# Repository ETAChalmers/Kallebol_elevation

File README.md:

# OLD deprecated Kallebol_elevation
This project has been abandoned and is not in use

Microcontroller and code for controlling elevation of kallebolen.

The microcontroller communicates via USB.

## Communication interface
 
### commandlist

 - ELEVATION HOME START    - Start homing of the elevationcontroller, this resets the current position
 - ELEVATION HOME STOP     - Stop homing
 - ELEVATION SET *Integer* - Set current position
 - ELEVATION GOTO *Integer* - Set current target position
 - ELEVATION STOP          - kind of a E-stop to the elevation controller, the onboard motor driver should not output any voltage
 - ELEVATION STOP RESET    - turn off the stop state
 - ELEVATION GET POSITION  - returns the current position of the controller
 - ELEVATION GET TARGET    - returns the target position of the controller
 - ELEVATION GET FLAGS     - returns the states of the controller
 - ELEVATION GET ALL       - returns all of the states and positions
 - LOAD LOAD1 [ON/OFF]     - turn on/off load 1
 - LOAD LOAD2 [ON/OFF]     - turn on/off load 2
 - LED ONBOARD [ON/OFF]    - turn on/off the MCUs onboard LED
 - LED PCB0 [ON/OFF]       - turn on/off LED 0 on the PCB
 - LED PCB1 [ON/OFF]       - turn on/off LED 0 on the PCB
 - LED PCB2 [ON/OFF]       - turn on/off LED 0 on the PCB
 - LED PCB3 [ON/OFF]       - turn on/off LED 0 on the PCB
 - RFSWITCH    (TBD)

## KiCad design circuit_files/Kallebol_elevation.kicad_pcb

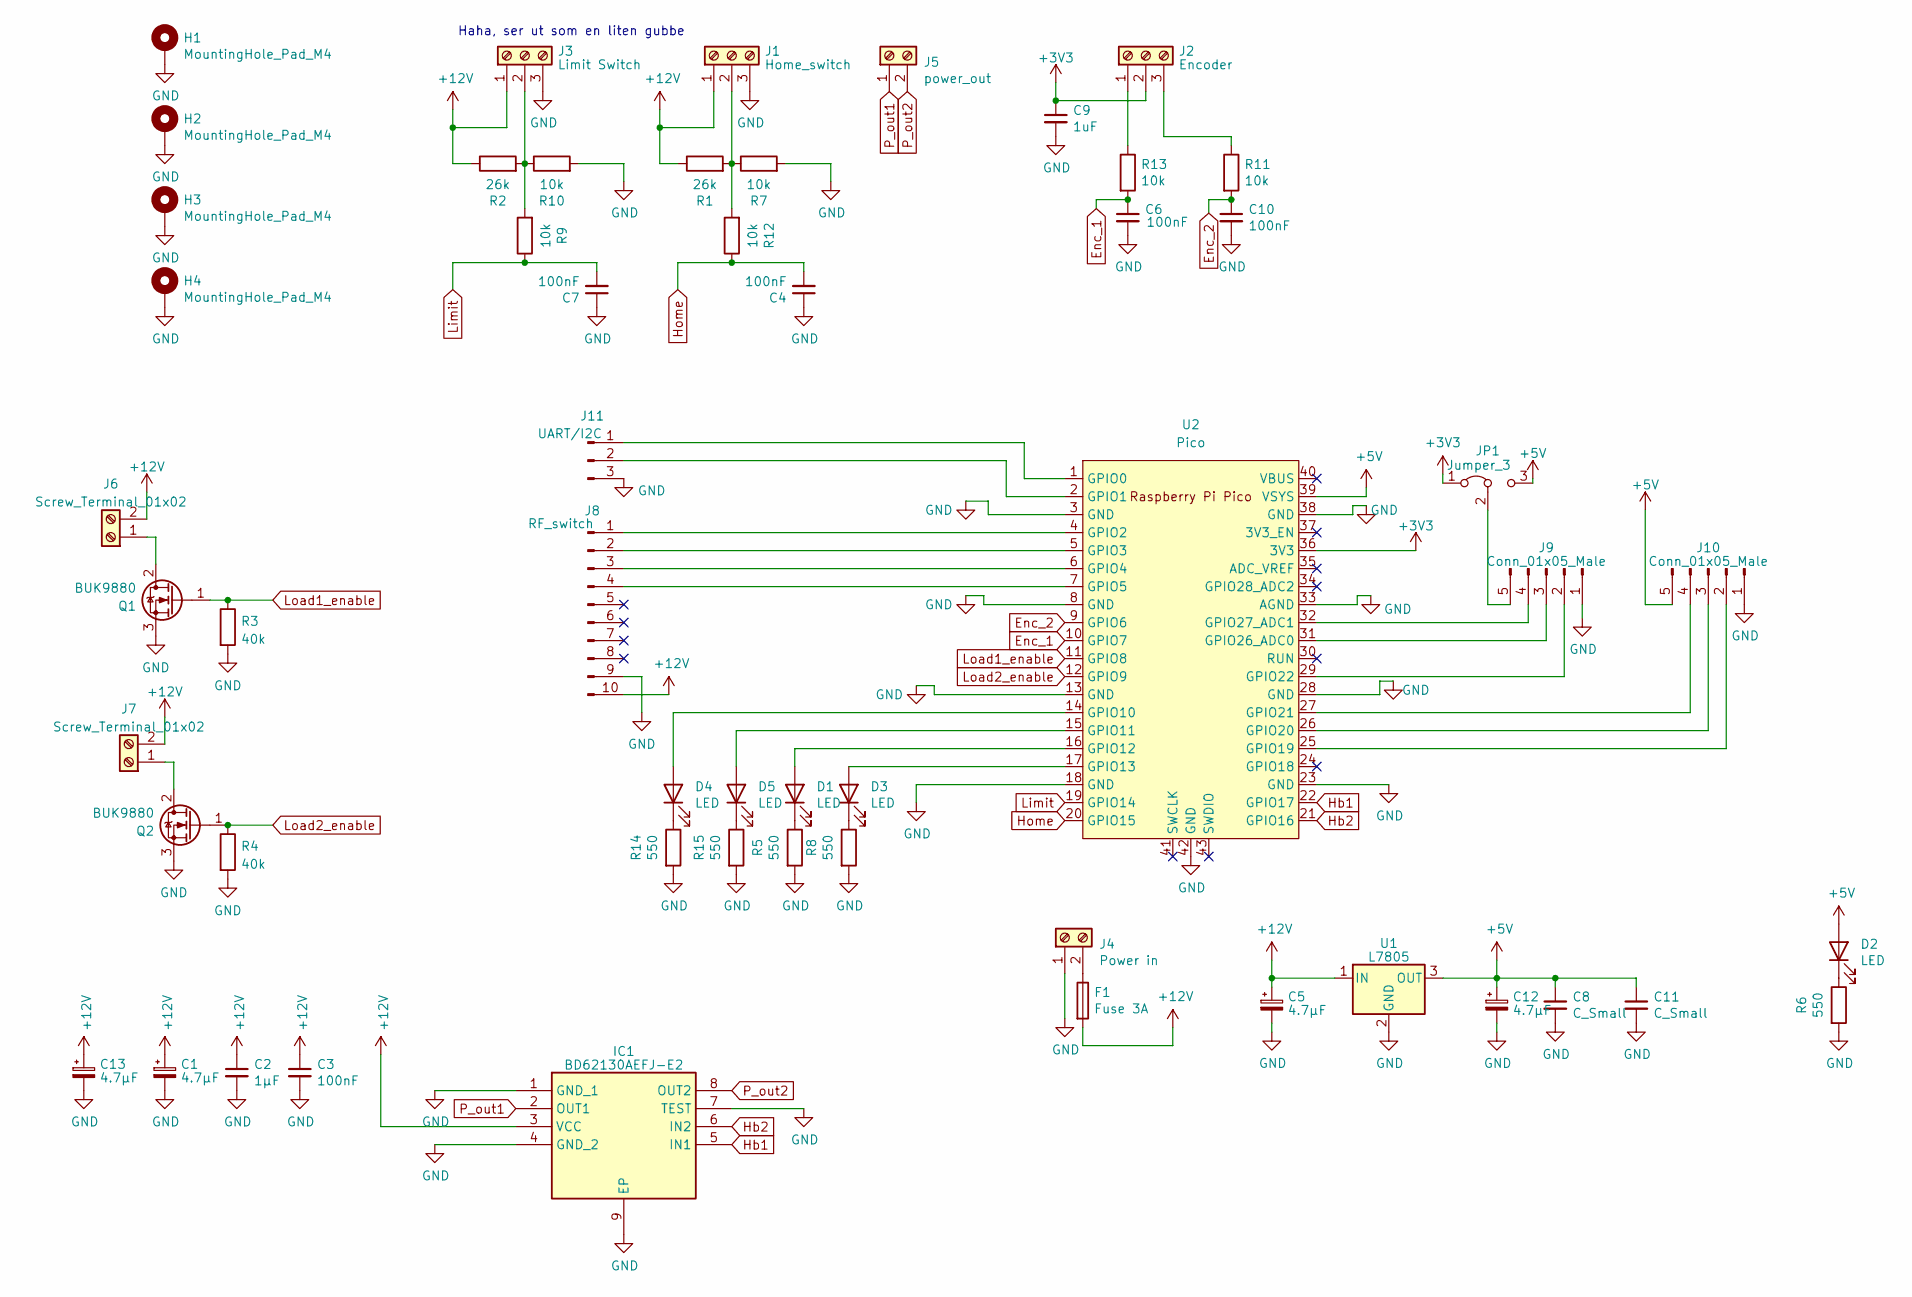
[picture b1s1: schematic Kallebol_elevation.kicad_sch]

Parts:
C1, C5, C12, C13: 4.7µF; CP_Elec_10x10
C2: 1µF; C_0603_1608Metric_Pad1.08x0.95mm_HandSolder
C3, C4, C6, C7, C10: 100nF; C_0603_1608Metric_Pad1.08x0.95mm_HandSolder
C8, C11: C_Small; C_0603_1608Metric_Pad1.08x0.95mm_HandSolder
C9: 1uF; C_0603_1608Metric_Pad1.08x0.95mm_HandSolder
D1, D2, D3, D4, D5: LED; LED_0603_1608Metric
F1: Fuse 3A; Fuseholder_Cylinder-5x20mm_Wuerth_696103101002-SMD_Horizont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
H1, H2, H3, H4: MountingHole_Pad_M4; MountingHole_4.3mm_M4_Pad
IC1: BD62130AEFJ-E2; SOIC127P600X100-9N; Mouser Part Number 755-BD62130AEFJ-E2
J1: Home_switch; TerminalBlock_Phoenix_MKDS-1,5-3_1x03_P5.00mm_Horizontal
J2: Encoder; TerminalBlock_Phoenix_MKDS-1,5-3_1x03_P5.00mm_Horizontal
J3: Limit Switch; TerminalBlock_Phoenix_MKDS-1,5-3_1x03_P5.00mm_Horizontal
J4: Power in; TerminalBlock_bornier-2_P5.08mm
J5: power_out; TerminalBlock_bornier-2_P5.08mm
J6, J7: Screw_Terminal_01x02; TerminalBlock_bornier-2_P5.08mm
J8: RF_switch; PinSocket_1x10_P2.54mm_Vertical
J9, J10: Conn_01x05_Male; PinSocket_1x05_P2.54mm_Vertical
J11: UART/I2C; PinSocket_1x03_P2.54mm_Vertical
JP1: Jumper_3; PinSocket_1x03_P2.54mm_Vertical
Q1, Q2: BUK9880; SOT-223-3_TabPin2
R1, R2: 26k; R_0603_1608Metric_Pad0.98x0.95mm_HandSolder
R3, R4: 40k; R_0603_1608Metric_Pad0.98x0.95mm_HandSolder
R5, R6, R8, R14, R15: 550; R_0603_1608Metric_Pad0.98x0.95mm_HandSolder
R7, R9, R10, R11, R12, R13: 10k; R_0603_1608Metric_Pad0.98x0.95mm_HandSolder
U1: L7805; SOT-223-3_TabPin2
U2: Pico; RPi_Pico_SMD_TH

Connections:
+3V3: C9.1, J2.2, JP1.1 (A), U2.36 (3V3)
+5V: C8.1, C11.1, C12.1, D2.2 (A), J10.5, JP1.3 (B), U1.3 (OUT), U2.39 (VSYS)
+12V: C1.1, C2.1, C3.1, C5.1, C13.1, F1.2, IC1.3 (VCC), J1.1, J3.1, J6.2, J7.2, J8.10, R1.1, R2.1, U1.1 (IN)
Enc_1: C6.1, R13.2, U2.10 (GPIO7)
Enc_2: C10.1, R11.2, U2.9 (GPIO6)
GND: C1.2, C2.2, C3.2, C4.1, C5.2, C6.2, C7.1, C8.2, C9.2, C10.2, C11.2, C12.2, C13.2, H1.1, H2.1, H3.1, H4.1, IC1.1 (GND_1), IC1.4 (GND_2), IC1.7 (TEST), IC1.9 (EP), J1.3, J3.3, J4.1, J8.9, J9.1, J10.1, J11.3, Q1.3 (S), Q2.3 (S), R3.2, R4.2, R5.2, R6.2, R7.2, R8.2, R10.2, R14.2, R15.2, U1.2 (GND), U2.3 (GND), U2.8 (GND), U2.13 (GND), U2.18 (GND), U2.23 (GND), U2.28 (GND), U2.33 (AGND), U2.38 (GND), U2.42 (GND)
Hb1: IC1.5 (IN1), U2.22 (GPIO17)
Hb2: IC1.6 (IN2), U2.21 (GPIO16)
Home: C4.2, R12.1, U2.20 (GPIO15)
Limit: C7.2, R9.1, U2.19 (GPIO14)
Load1_enable: Q1.1 (G), R3.1, U2.11 (GPIO8)
Load2_enable: Q2.1 (G), R4.1, U2.12 (GPIO9)
unnamed: D1.2 (A), U2.16 (GPIO12)
unnamed: D1.1 (K), R5.1
unnamed: D2.1 (K), R6.1
unnamed: D3.2 (A), U2.17 (GPIO13)
unnamed: D3.1 (K), R8.1
unnamed: D4.2 (A), U2.14 (GPIO10)
unnamed: D4.1 (K), R14.1
unnamed: D5.2 (A), U2.15 (GPIO11)
unnamed: D5.1 (K), R15.1
unnamed: J1.2, R1.2, R7.1, R12.2
unnamed: J2.1, R13.1
unnamed: J2.3, R11.1
unnamed: J3.2, R2.2, R9.2, R10.1
unnamed: F1.1, J4.2
unnamed: J6.1, Q1.2 (D)
unnamed: J7.1, Q2.2 (D)
unnamed: J8.1, U2.4 (GPIO2)
unnamed: J8.2, U2.5 (GPIO3)
unnamed: J8.3, U2.6 (GPIO4)
unnamed: J8.4, U2.7 (GPIO5)
unnamed: J9.2, U2.29 (GPIO22)
unnamed: J9.3, U2.31 (GPIO26_ADC0)
unnamed: J9.4, U2.32 (GPIO27_ADC1)
unnamed: J9.5, JP1.2 (C)
unnamed: J10.2, U2.25 (GPIO19)
unnamed: J10.3, U2.26 (GPIO20)
unnamed: J10.4, U2.27 (GPIO21)
unnamed: J11.1, U2.1 (GPIO0)
unnamed: J11.2, U2.2 (GPIO1)
P_out1: IC1.2 (OUT1), J5.1
P_out2: IC1.8 (OUT2), J5.2

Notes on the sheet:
Haha, ser ut som en liten gubbe

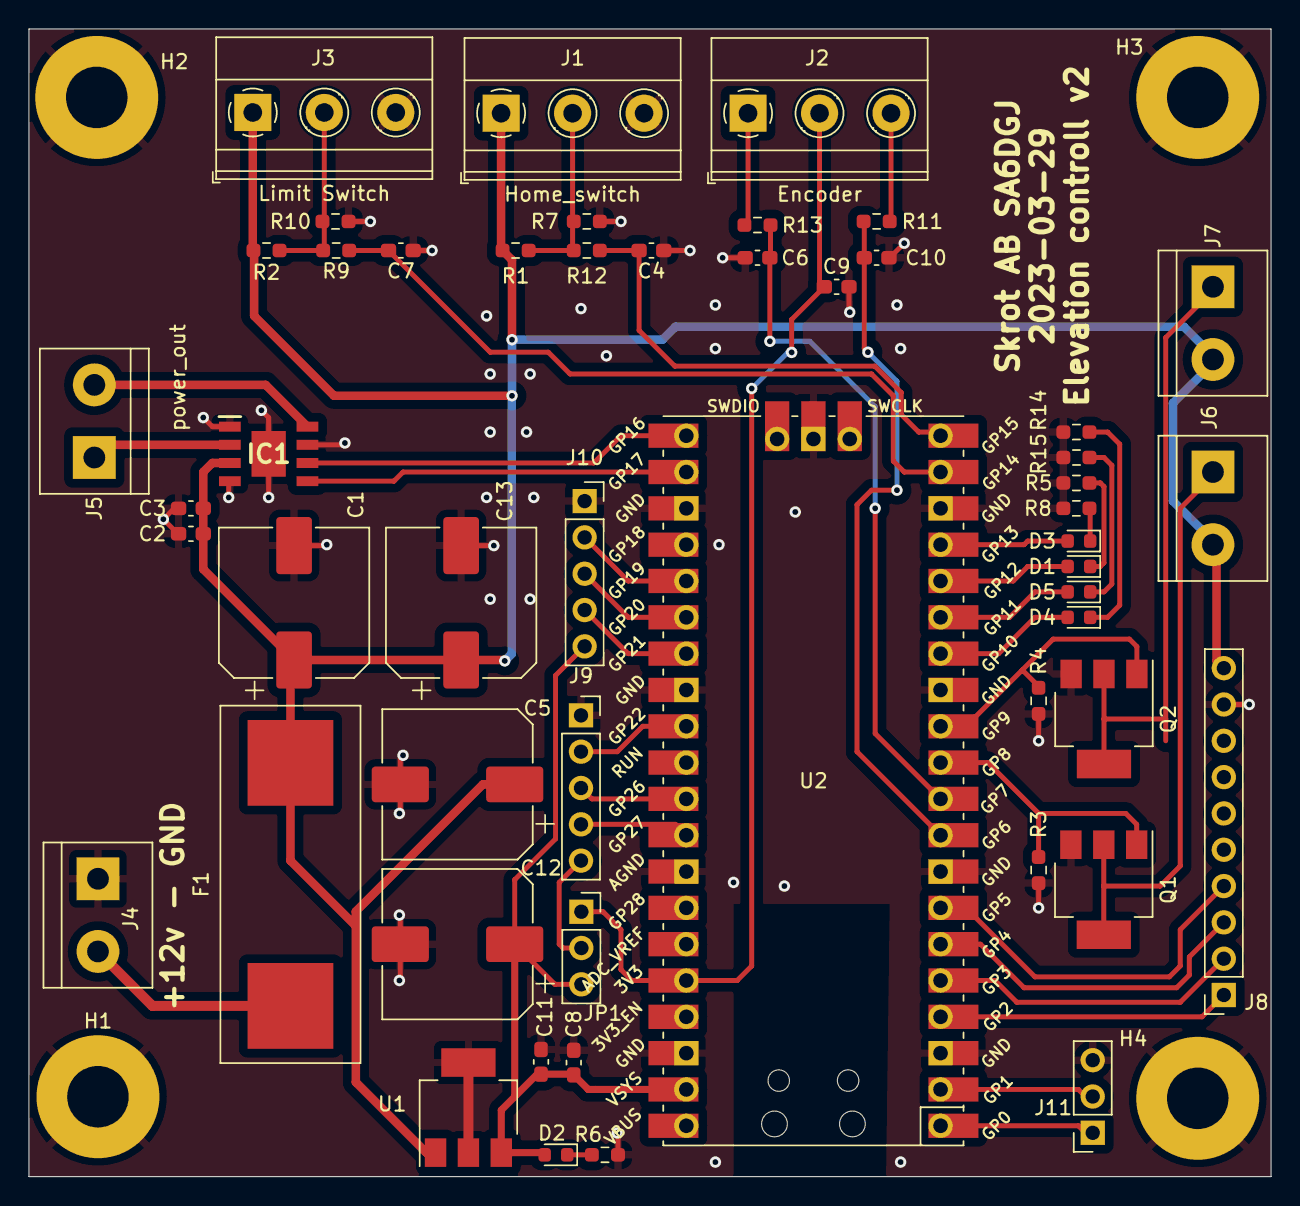
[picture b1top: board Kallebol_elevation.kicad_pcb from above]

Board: 2 copper layers, 86.9 x 80.3 mm, 55 parts (0 on the bottom side), 43 nets.

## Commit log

2022-01-10 added circuitboard project files
2022-01-10 restuctuing of files
2022-01-10 cleanup
2022-01-10 added gitignore
2022-07-08 renamed folder to make MPLAB happy
2022-07-08 adapted for compilation with XC8 v2 C99
2022-07-08 added echo on recived UART commands
2022-07-14 adapting for adaptive data packages
2022-07-15 added comments and more commands
2022-07-16 added the use of latchregisters to remove read-modify-write problems
2022-07-16 removed TX capabilities and fixed dead-end state
2022-07-16 fixed 16-bit data packeges being in the incorrect order
2022-09-20 interupts on pin does not work
2022-09-24 revert to monkey
2022-09-24 UART and goto movements working, minimum working product
2022-09-24 Fixed homing, deployable
2022-10-23 Added a minimum workable elevation controll
2023-03-04 started a new revision with a raspberry pico as base
2023-03-11 added symbol for DMC3021 and cleaned project files
2023-03-11 added basic driver circuit
2023-03-11 added BD62130A schematic symbol, to be used as driver circuit
2023-03-11 elevation part of the board functional
2023-03-11 merged functionality with the GPIO fanout board
2023-03-11 sch seems done
2023-03-29 layout done
2023-03-29 added production files
2023-03-29 added PDF files
2023-03-29 fixed issue with reversed mosfet
2023-05-10 started to implement the code for the new elevation controller
2023-05-15 tested on hardware, encoder works
2023-06-03 added small tveaks to elevation move commands
2023-06-10 Fixed syntax and made the motor move
2023-06-10 fixed bug with motorcontroll not stopping
2023-06-10 added better debug and output
2023-06-10 added debug output for pins
2023-06-10 added option to change polarity of hardware switches
2023-06-10 minor changes
2023-06-11 Chnaged polarity of homing/limit switch
2023-06-11 fixed homeing sequence
2023-06-11 fixed better debug and made it deployable
2023-07-14 added custom printer function that defines message length and terminates with \r
2024-07-27 fixed spammy status messages
2024-10-02 added a blinking LED of unknown speed
2024-10-02 fixed syntax error
2024-10-02 fixed issue with ELEVATION GET ALL crashing the program
2025-04-05 Last commit
